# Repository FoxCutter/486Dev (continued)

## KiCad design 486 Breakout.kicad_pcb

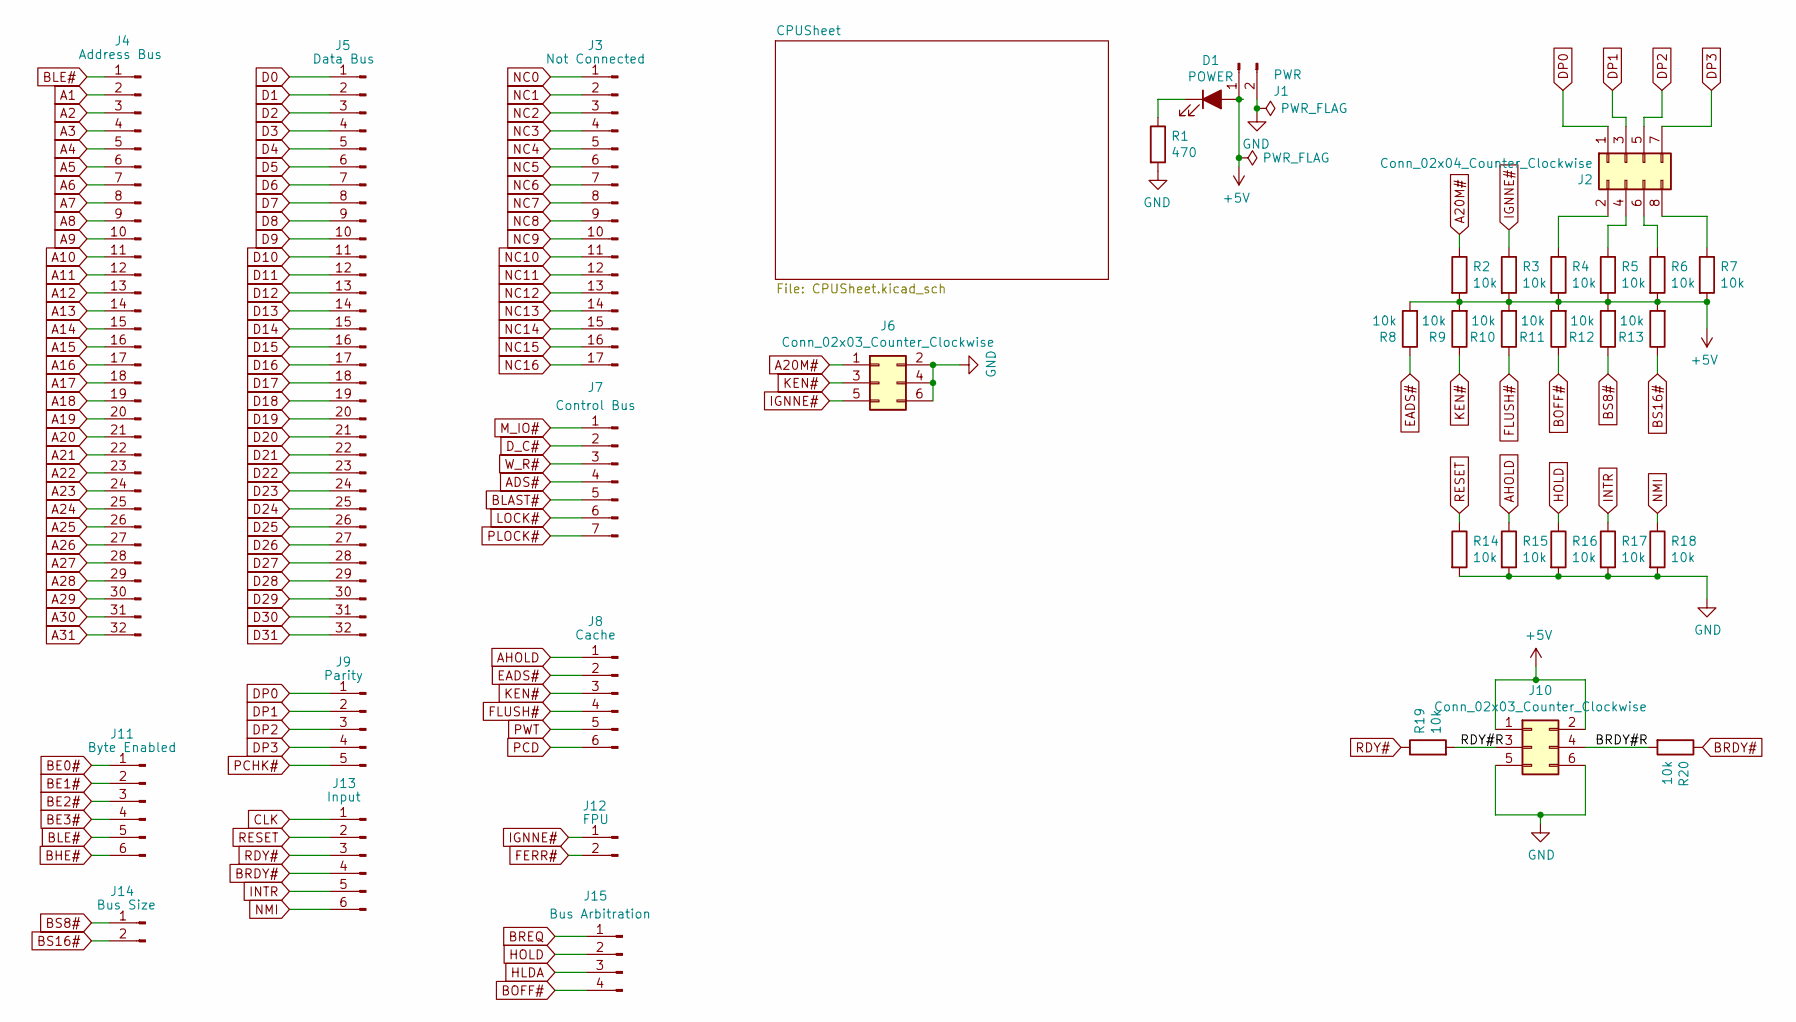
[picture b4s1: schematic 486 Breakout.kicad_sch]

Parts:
D1: POWER; LED_D3.0mm
J1: PWR; PinHeader_1x02_P2.54mm_Vertical
J2: Conn_02x04_Counter_Clockwise; PinHeader_2x04_P2.54mm_Vertical
J3: Not Connected; PinHeader_1x17_P2.54mm_Vertical
J4: Address Bus; PinHeader_1x32_P2.54mm_Vertical
J5: Data Bus; PinHeader_1x32_P2.54mm_Vertical
J6, J10: Conn_02x03_Counter_Clockwise; PinHeader_2x03_P2.54mm_Vertical
J7: Control Bus; PinHeader_1x07_P2.54mm_Vertical
J8: Cache; PinHeader_1x06_P2.54mm_Vertical
J9: Parity; PinHeader_1x05_P2.54mm_Vertical
J11: Byte Enabled; PinHeader_1x06_P2.54mm_Vertical
J12: FPU; PinHeader_1x02_P2.54mm_Vertical
J13: Input; PinHeader_1x06_P2.54mm_Vertical
J14: Bus Size; PinHeader_1x02_P2.54mm_Vertical
J15: Bus Arbitration; PinHeader_1x04_P2.54mm_Vertical
R1: 470; R_Axial_DIN0204_L3.6mm_D1.6mm_P7.62mm_Horizontal
R2, R3, R4, R5, R6, R7, R8, R9, R10, R11, R12, R13, R14, R15, R16, R17, R18, R19, R20: 10k; R_Axial_DIN0204_L3.6mm_D1.6mm_P7.62mm_Horizontal

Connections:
+5V: D1.2 (A), J1.1, J10.1, J10.2, R2.2, R3.2, R4.2, R5.2, R6.2, R7.2, R8.2, R9.2, R10.2, R11.2, R12.2, R13.2; also elsewhere on the board
/BRDY#R: J10.4, R20.2
/RDY#R: J10.3, R19.2
A1: J4.2; also elsewhere on the board
A2: J4.3; also elsewhere on the board
A3: J4.4; also elsewhere on the board
A4: J4.5; also elsewhere on the board
A5: J4.6; also elsewhere on the board
A6: J4.7; also elsewhere on the board
A7: J4.8; also elsewhere on the board
A8: J4.9; also elsewhere on the board
A9: J4.10; also elsewhere on the board
A10: J4.11; also elsewhere on the board
A11: J4.12; also elsewhere on the board
A12: J4.13; also elsewhere on the board
A13: J4.14; also elsewhere on the board
A14: J4.15; also elsewhere on the board
A15: J4.16; also elsewhere on the board
A16: J4.17; also elsewhere on the board
A17: J4.18; also elsewhere on the board
A18: J4.19; also elsewhere on the board
A19: J4.20; also elsewhere on the board
A20: J4.21; also elsewhere on the board
A20M#: J6.1, R2.1; also elsewhere on the board
A21: J4.22; also elsewhere on the board
A22: J4.23; also elsewhere on the board
A23: J4.24; also elsewhere on the board
A24: J4.25; also elsewhere on the board
A25: J4.26; also elsewhere on the board
A26: J4.27; also elsewhere on the board
A27: J4.28; also elsewhere on the board
A28: J4.29; also elsewhere on the board
A29: J4.30; also elsewhere on the board
A30: J4.31; also elsewhere on the board
A31: J4.32; also elsewhere on the board
ADS#: J7.4; also elsewhere on the board
AHOLD: J8.1, R15.1; also elsewhere on the board
BE0#: J11.1; also elsewhere on the board
BE1#: J11.2; also elsewhere on the board
BE2#: J11.3; also elsewhere on the board
BE3#: J11.4; also elsewhere on the board
BHE#: J11.6; also elsewhere on the board
BLAST#: J7.5; also elsewhere on the board
BLE#: J4.1, J11.5; also elsewhere on the board
BOFF#: J15.4, R11.1; also elsewhere on the board
BRDY#: J13.4, R20.1; also elsewhere on the board
BREQ: J15.1; also elsewhere on the board
BS8#: J14.1, R12.1; also elsewhere on the board
BS16#: J14.2, R13.1; also elsewhere on the board
CLK: J13.1; also elsewhere on the board
D0: J5.1; also elsewhere on the board
D1: J5.2; also elsewhere on the board
D2: J5.3; also elsewhere on the board
D3: J5.4; also elsewhere on the board
D4: J5.5; also elsewhere on the board
D5: J5.6; also elsewhere on the board
D6: J5.7; also elsewhere on the board
D7: J5.8; also elsewhere on the board
D8: J5.9; also elsewhere on the board
D9: J5.10; also elsewhere on the board
D10: J5.11; also elsewhere on the board
D11: J5.12; also elsewhere on the board
D12: J5.13; also elsewhere on the board
D13: J5.14; also elsewhere on the board
D14: J5.15; also elsewhere on the board
D15: J5.16; also elsewhere on the board
D16: J5.17; also elsewhere on the board
D17: J5.18; also elsewhere on the board
D18: J5.19; also elsewhere on the board
D19: J5.20; also elsewhere on the board
D20: J5.21; also elsewhere on the board
D21: J5.22; also elsewhere on the board
D22: J5.23; also elsewhere on the board
D23: J5.24; also elsewhere on the board
D24: J5.25; also elsewhere on the board
D25: J5.26; also elsewhere on the board
D26: J5.27; also elsewhere on the board
D27: J5.28; also elsewhere on the board
D28: J5.29; also elsewhere on the board
D29: J5.30; also elsewhere on the board
D30: J5.31; also elsewhere on the board
D31: J5.32; also elsewhere on the board
DP0: J2.1, J9.1; also elsewhere on the board
DP1: J2.3, J9.2; also elsewhere on the board
DP2: J2.5, J9.3; also elsewhere on the board
DP3: J2.7, J9.4; also elsewhere on the board
D_C#: J7.2; also elsewhere on the board
EADS#: J8.2, R8.1; also elsewhere on the board
FERR#: J12.2; also elsewhere on the board
FLUSH#: J8.4, R10.1; also elsewhere on the board
GND: J1.2, J6.2, J6.4, J6.6, J10.5, J10.6, R1.2, R14.2, R15.2, R16.2, R17.2, R18.2; also elsewhere on the board
HLDA: J15.3; also elsewhere on the board
HOLD: J15.2, R16.1; also elsewhere on the board
IGNNE#: J6.5, J12.1, R3.1; also elsewhere on the board
INTR: J13.5, R17.1; also elsewhere on the board
KEN#: J6.3, J8.3, R9.1; also elsewhere on the board
LOCK#: J7.6; also elsewhere on the board
M_IO#: J7.1; also elsewhere on the board
NC0: J3.1; also elsewhere on the board
NC1: J3.2; also elsewhere on the board
NC2: J3.3; also elsewhere on the board
NC3: J3.4; also elsewhere on the board
NC4: J3.5; also elsewhere on the board
NC5: J3.6; also elsewhere on the board
NC6: J3.7; also elsewhere on the board
NC7: J3.8; also elsewhere on the board
NC8: J3.9; also elsewhere on the board
NC9: J3.10; also elsewhere on the board
NC10: J3.11; also elsewhere on the board
NC11: J3.12; also elsewhere on the board
NC12: J3.13; also elsewhere on the board
NC13: J3.14; also elsewhere on the board
NC14: J3.15; also elsewhere on the board
NC15: J3.16; also elsewhere on the board
NC16: J3.17; also elsewhere on the board
NMI: J13.6, R18.1; also elsewhere on the board
unnamed: D1.1 (K), R1.1
unnamed: J2.2, R4.1
unnamed: J2.4, R5.1
unnamed: J2.6, R6.1
unnamed: J2.8, R7.1
PCD: J8.6; also elsewhere on the board
PCHK#: J9.5; also elsewhere on the board
PLOCK#: J7.7; also elsewhere on the board
PWT: J8.5; also elsewhere on the board
RDY#: J13.3, R19.1; also elsewhere on the board
RESET: J13.2, R14.1; also elsewhere on the board
W_R#: J7.3; also elsewhere on the board

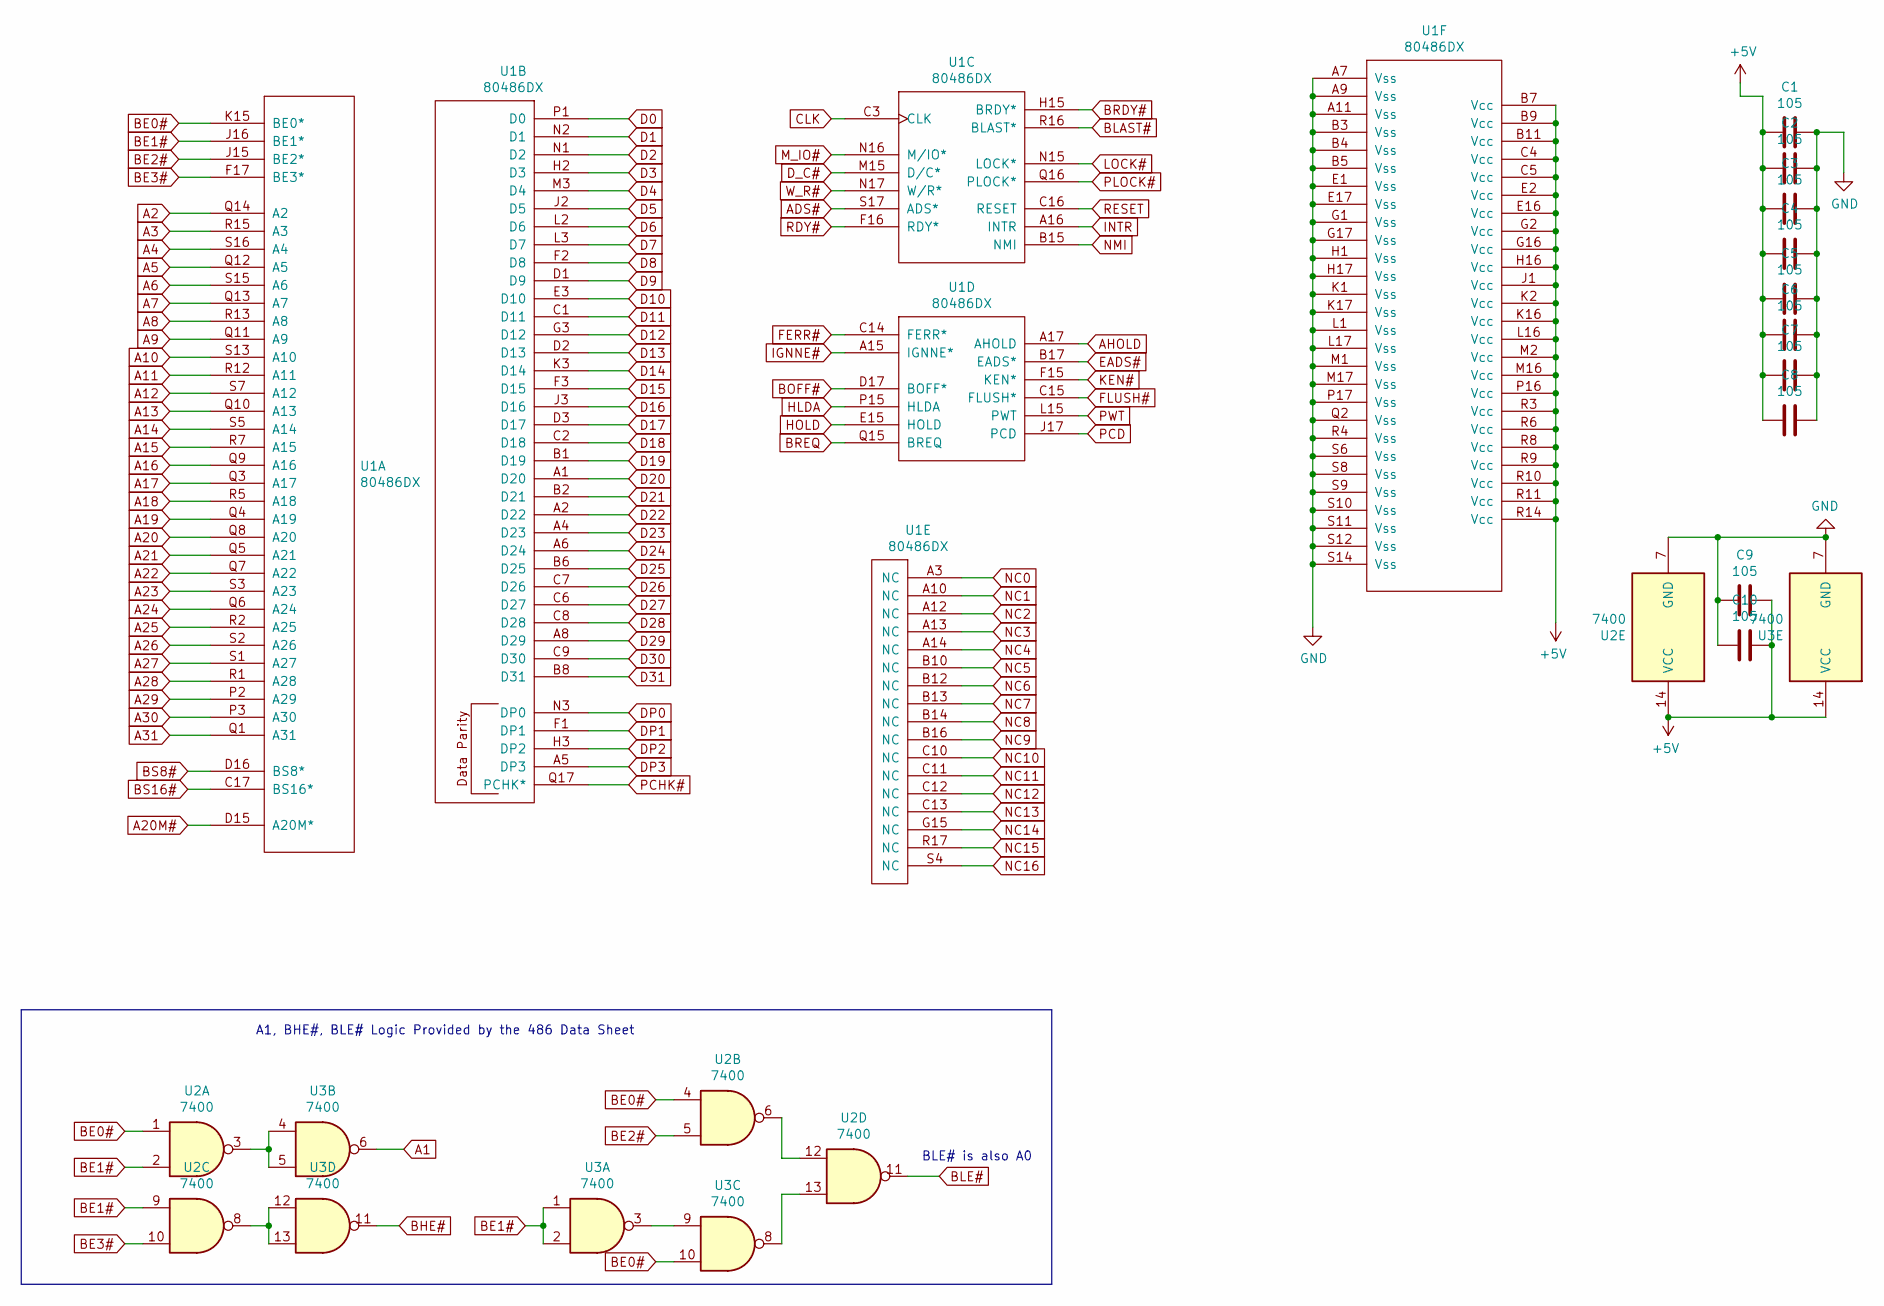
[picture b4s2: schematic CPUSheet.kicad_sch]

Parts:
C1, C2, C3, C4, C5, C6, C7, C8, C9, C10: 105; C_Disc_D3.0mm_W1.6mm_P2.50mm
U1: 80486DX; PGA169
U2, U3: 7400; DIP-14_W7.62mm_Socket

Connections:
+5V: C1.2, C2.2, C3.2, C4.2, C5.2, C6.2, C7.2, C8.2, C9.1, C10.1, U1.B7 (Vcc), U1.B9 (Vcc), U1.B11 (Vcc), U1.C4 (Vcc), U1.C5 (Vcc), U1.E2 (Vcc), U1.E16 (Vcc), U1.G2 (Vcc), U1.G16 (Vcc), U1.H16 (Vcc), U1.J1 (Vcc), U1.K2 (Vcc), U1.K16 (Vcc), U1.L16 (Vcc), U1.M2 (Vcc), U1.M16 (Vcc), U1.P16 (Vcc), U1.R3 (Vcc), U1.R6 (Vcc), U1.R8 (Vcc), U1.R9 (Vcc), U1.R10 (Vcc), U1.R11 (Vcc), U1.R14 (Vcc), U2.14 (VCC), U3.14 (VCC); also elsewhere on the board
A1: U3.6; also elsewhere on the board
A2: U1.Q14 (A2); also elsewhere on the board
A3: U1.R15 (A3); also elsewhere on the board
A4: U1.S16 (A4); also elsewhere on the board
A5: U1.Q12 (A5); also elsewhere on the board
A6: U1.S15 (A6); also elsewhere on the board
A7: U1.Q13 (A7); also elsewhere on the board
A8: U1.R13 (A8); also elsewhere on the board
A9: U1.Q11 (A9); also elsewhere on the board
A10: U1.S13 (A10); also elsewhere on the board
A11: U1.R12 (A11); also elsewhere on the board
A12: U1.S7 (A12); also elsewhere on the board
A13: U1.Q10 (A13); also elsewhere on the board
A14: U1.S5 (A14); also elsewhere on the board
A15: U1.R7 (A15); also elsewhere on the board
A16: U1.Q9 (A16); also elsewhere on the board
A17: U1.Q3 (A17); also elsewhere on the board
A18: U1.R5 (A18); also elsewhere on the board
A19: U1.Q4 (A19); also elsewhere on the board
A20: U1.Q8 (A20); also elsewhere on the board
A20M#: U1.D15 (A20M*); also elsewhere on the board
A21: U1.Q5 (A21); also elsewhere on the board
A22: U1.Q7 (A22); also elsewhere on the board
A23: U1.S3 (A23); also elsewhere on the board
A24: U1.Q6 (A24); also elsewhere on the board
A25: U1.R2 (A25); also elsewhere on the board
A26: U1.S2 (A26); also elsewhere on the board
A27: U1.S1 (A27); also elsewhere on the board
A28: U1.R1 (A28); also elsewhere on the board
A29: U1.P2 (A29); also elsewhere on the board
A30: U1.P3 (A30); also elsewhere on the board
A31: U1.Q1 (A31); also elsewhere on the board
ADS#: U1.S17 (ADS*); also elsewhere on the board
AHOLD: U1.A17 (AHOLD); also elsewhere on the board
BE0#: U1.K15 (BE0*), U2.1, U2.4, U3.10; also elsewhere on the board
BE1#: U1.J16 (BE1*), U2.2, U2.9, U3.1, U3.2; also elsewhere on the board
BE2#: U1.J15 (BE2*), U2.5; also elsewhere on the board
BE3#: U1.F17 (BE3*), U2.10; also elsewhere on the board
BHE#: U3.11; also elsewhere on the board
BLAST#: U1.R16 (BLAST*); also elsewhere on the board
BLE#: U2.11; also elsewhere on the board
BOFF#: U1.D17 (BOFF*); also elsewhere on the board
BRDY#: U1.H15 (BRDY*); also elsewhere on the board
BREQ: U1.Q15 (BREQ); also elsewhere on the board
BS8#: U1.D16 (BS8*); also elsewhere on the board
BS16#: U1.C17 (BS16*); also elsewhere on the board
CLK: U1.C3 (CLK); also elsewhere on the board
D0: U1.P1 (D0); also elsewhere on the board
D1: U1.N2 (D1); also elsewhere on the board
D2: U1.N1 (D2); also elsewhere on the board
D3: U1.H2 (D3); also elsewhere on the board
D4: U1.M3 (D4); also elsewhere on the board
D5: U1.J2 (D5); also elsewhere on the board
D6: U1.L2 (D6); also elsewhere on the board
D7: U1.L3 (D7); also elsewhere on the board
D8: U1.F2 (D8); also elsewhere on the board
D9: U1.D1 (D9); also elsewhere on the board
D10: U1.E3 (D10); also elsewhere on the board
D11: U1.C1 (D11); also elsewhere on the board
D12: U1.G3 (D12); also elsewhere on the board
D13: U1.D2 (D13); also elsewhere on the board
D14: U1.K3 (D14); also elsewhere on the board
D15: U1.F3 (D15); also elsewhere on the board
D16: U1.J3 (D16); also elsewhere on the board
D17: U1.D3 (D17); also elsewhere on the board
D18: U1.C2 (D18); also elsewhere on the board
D19: U1.B1 (D19); also elsewhere on the board
D20: U1.A1 (D20); also elsewhere on the board
D21: U1.B2 (D21); also elsewhere on the board
D22: U1.A2 (D22); also elsewhere on the board
D23: U1.A4 (D23); also elsewhere on the board
D24: U1.A6 (D24); also elsewhere on the board
D25: U1.B6 (D25); also elsewhere on the board
D26: U1.C7 (D26); also elsewhere on the board
D27: U1.C6 (D27); also elsewhere on the board
D28: U1.C8 (D28); also elsewhere on the board
D29: U1.A8 (D29); also elsewhere on the board
D30: U1.C9 (D30); also elsewhere on the board
D31: U1.B8 (D31); also elsewhere on the board
DP0: U1.N3 (DP0); also elsewhere on the board
DP1: U1.F1 (DP1); also elsewhere on the board
DP2: U1.H3 (DP2); also elsewhere on the board
DP3: U1.A5 (DP3); also elsewhere on the board
D_C#: U1.M15 (D/C*); also elsewhere on the board
EADS#: U1.B17 (EADS*); also elsewhere on the board
FERR#: U1.C14 (FERR*); also elsewhere on the board
FLUSH#: U1.C15 (FLUSH*); also elsewhere on the board
GND: C1.1, C2.1, C3.1, C4.1, C5.1, C6.1, C7.1, C8.1, C9.2, C10.2, U1.A7 (Vss), U1.A9 (Vss), U1.A11 (Vss), U1.B3 (Vss), U1.B4 (Vss), U1.B5 (Vss), U1.E1 (Vss), U1.E17 (Vss), U1.G1 (Vss), U1.G17 (Vss), U1.H1 (Vss), U1.H17 (Vss), U1.K1 (Vss), U1.K17 (Vss), U1.L1 (Vss), U1.L17 (Vss), U1.M1 (Vss), U1.M17 (Vss), U1.P17 (Vss), U1.Q2 (Vss), U1.R4 (Vss), U1.S6 (Vss), U1.S8 (Vss), U1.S9 (Vss), U1.S10 (Vss), U1.S11 (Vss), U1.S12 (Vss), U1.S14 (Vss), U2.7 (GND), U3.7 (GND); also elsewhere on the board
HLDA: U1.P15 (HLDA); also elsewhere on the board
HOLD: U1.E15 (HOLD); also elsewhere on the board
IGNNE#: U1.A15 (IGNNE*); also elsewhere on the board
INTR: U1.A16 (INTR); also elsewhere on the board
KEN#: U1.F15 (KEN*); also elsewhere on the board
LOCK#: U1.N15 (LOCK*); also elsewhere on the board
M_IO#: U1.N16 (M/IO*); also elsewhere on the board
NC0: U1.A3 (NC); also elsewhere on the board
NC1: U1.A10 (NC); also elsewhere on the board
NC2: U1.A12 (NC); also elsewhere on the board
NC3: U1.A13 (NC); also elsewhere on the board
NC4: U1.A14 (NC); also elsewhere on the board
NC5: U1.B10 (NC); also elsewhere on the board
NC6: U1.B12 (NC); also elsewhere on the board
NC7: U1.B13 (NC); also elsewhere on the board
NC8: U1.B14 (NC); also elsewhere on the board
NC9: U1.B16 (NC); also elsewhere on the board
NC10: U1.C10 (NC); also elsewhere on the board
NC11: U1.C11 (NC); also elsewhere on the board
NC12: U1.C12 (NC); also elsewhere on the board
NC13: U1.C13 (NC); also elsewhere on the board
NC14: U1.G15 (NC); also elsewhere on the board
NC15: U1.R17 (NC); also elsewhere on the board
NC16: U1.S4 (NC); also elsewhere on the board
NMI: U1.B15 (NMI); also elsewhere on the board
unnamed: U2.3, U3.4, U3.5
unnamed: U2.8, U3.12, U3.13
unnamed: U2.6, U2.12
unnamed: U2.13, U3.8
unnamed: U3.3, U3.9
PCD: U1.J17 (PCD); also elsewhere on the board
PCHK#: U1.Q17 (PCHK*); also elsewhere on the board
PLOCK#: U1.Q16 (PLOCK*); also elsewhere on the board
PWT: U1.L15 (PWT); also elsewhere on the board
RDY#: U1.F16 (RDY*); also elsewhere on the board
RESET: U1.C16 (RESET); also elsewhere on the board
W_R#: U1.N17 (W/R*); also elsewhere on the board

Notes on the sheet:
A1, BHE#, BLE# Logic Provided by the 486 Data Sheet
BLE# is also A0

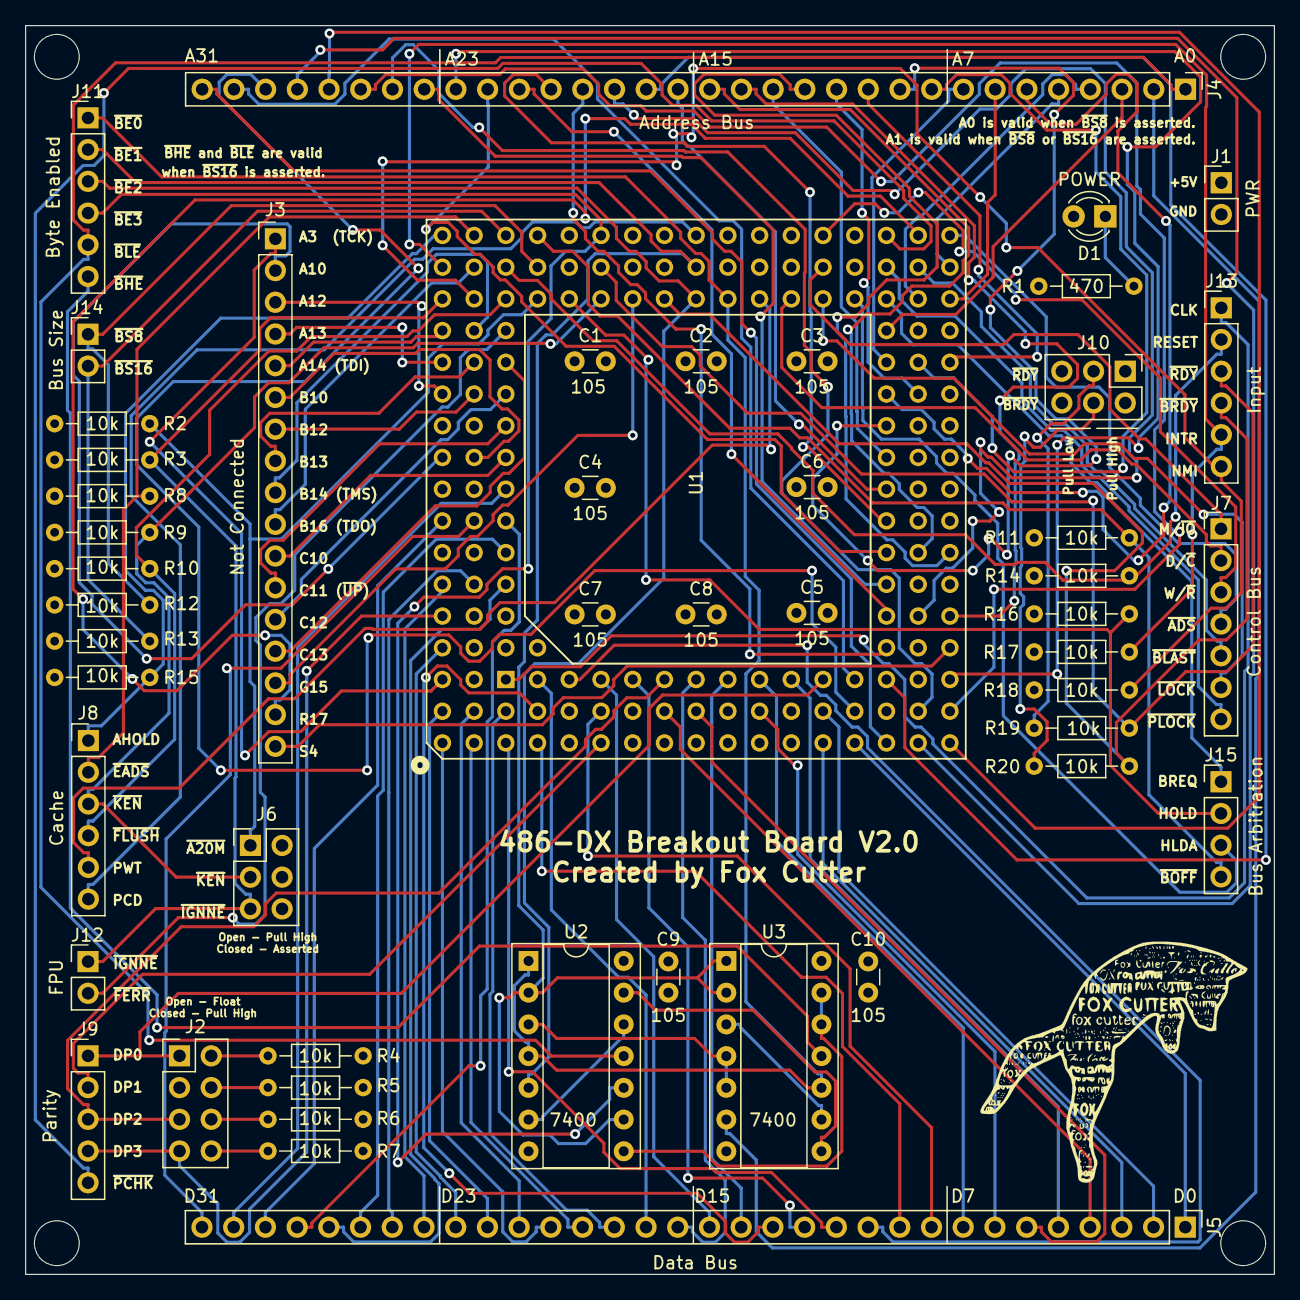
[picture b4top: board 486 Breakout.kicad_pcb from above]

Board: 4 copper layers, 100.0 x 100.0 mm, 49 parts (0 on the bottom side), 133 nets.

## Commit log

2023-01-10 Added a 486 beakout pcb
2023-02-01 V2 of the board
2023-02-05 * Update to Kicad 6
2023-03-17 Adding License and Readme for the 486 Breakout board
2023-03-17 Updating the 486 Breakout Board
2023-03-17 Updating png
2023-03-17 Markdown corrections
2023-03-22 Moving FIles
2023-03-26 Adding TestRom1
2023-04-05 * Updating the 486 PCB * TestRom2 added
2023-04-22 * TestRom3
2023-05-07 UART testing
2023-05-18 Adding first draft of 486 support board
2023-05-29 Minor PCB updates, and adding Gerber files
2023-06-06 Image file update
2023-06-12 * Layout Template for eurocard format * 486 Board updated to new layout * Support board draft * Added 6u eurocard backplane meant for ATX case
